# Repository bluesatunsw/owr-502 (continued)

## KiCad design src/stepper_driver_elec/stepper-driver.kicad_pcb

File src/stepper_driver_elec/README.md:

# Stepper Driver

A device to drive up to four high-current (10A peak, 5A continuous) bipolar stepper motors or eight brushed DC motors/solenoids. External sensors/low power devices may also be attached. It complies with the common device specification 2025-04.

## Steppers

Each stepper motor channel is driven by a TMC5160 controller. These controllers operate by driving two external full bridges, allowing for significantly more current to be delivered compared to devices with internal MOSFETs (such as the TMC2160).

Communication between the MCU and stepper controllers is performed using SPI. To allow for precise velocity control, the MCU provides a clock signal (using the MCO pin) to the clock input of the stepper drivers. Weak parallel termination (470R) is applied to reduce overshoot. The VSA rail of each controller is fed from the device 12V rail to reduce the heat generated by the internal linear regulators. For safety, the `DRV_ENN` pin of each stepper should be tied to a common line controlled by the MCU, externally pulled high.

The coils of the stepper motors are connected using a 4-pin JST-VH connector. A 6-pin JST-PA connector exposes the reference switch and A/B encoder pins of the controller, along with 3V3 and GND.

The TMC5160 datasheet states that 100u of capacitance per amp of output current is required; however, this requirement can be reduced significantly by using polymer capacitors, which have a very low ESR. A 220u capacitor (HV1H227M1010PZ) per channel should be sufficient.

### MOSFETs
| Manufacturer | Model        | Max Voltage | Peak Current | Continuous Current | RDS_on |
|--------------|--------------|-------------|--------------|--------------------|--------|
| Infineon     | BTN7030-1EPA | 28V         | 17A          |7A       | |

### Coil Pinout

| Pin | Signal | Colour |
| --- | ------ | ------ |
|  1  | `-A`   | Black  |
|  2  | `+A`   | Red    |
|  3  | `-B`   | Brown  |
|  4  | `+B`   | White  |

### Sensor Pinout

| Pin | Signal | Colour |
| --- | ------ | ------ |
|  1  | `GND`  | Black  |
|  2  | `VDD`  | Red    |
|  3  | `REFL` | Yellow |
|  4  | `REFR` | Green  |
|  5  | `ENCA` | Blue   |
|  6  | `ENCB` | Purple |

## Breakout Port

External sensors and low-power devices may be connected via a 24-pin JST-ZPD breakout header exposing:
- power from the VDD, 12V and VBUS;
- digital communication via I2C, SPI and UART/USART;
- digital GPIO including timer channels; and
- analog GPIO including op-amp and comparator channels.

The IO pins routed to the breakout port are not otherwise used for any other purpose.

**[TODO] Specify pinout**

## Internal Sensors

- Each stepper channel has an NTC thermistor (NCP15XH103F03RC) for temperature monitoring.
- A 6-axis IMU (ASM330LHH) and 3-axis magnetometer (LIS2MDL), both communicating over I2C, may optionally be installed to allow for groundstation use and advanced control modes.

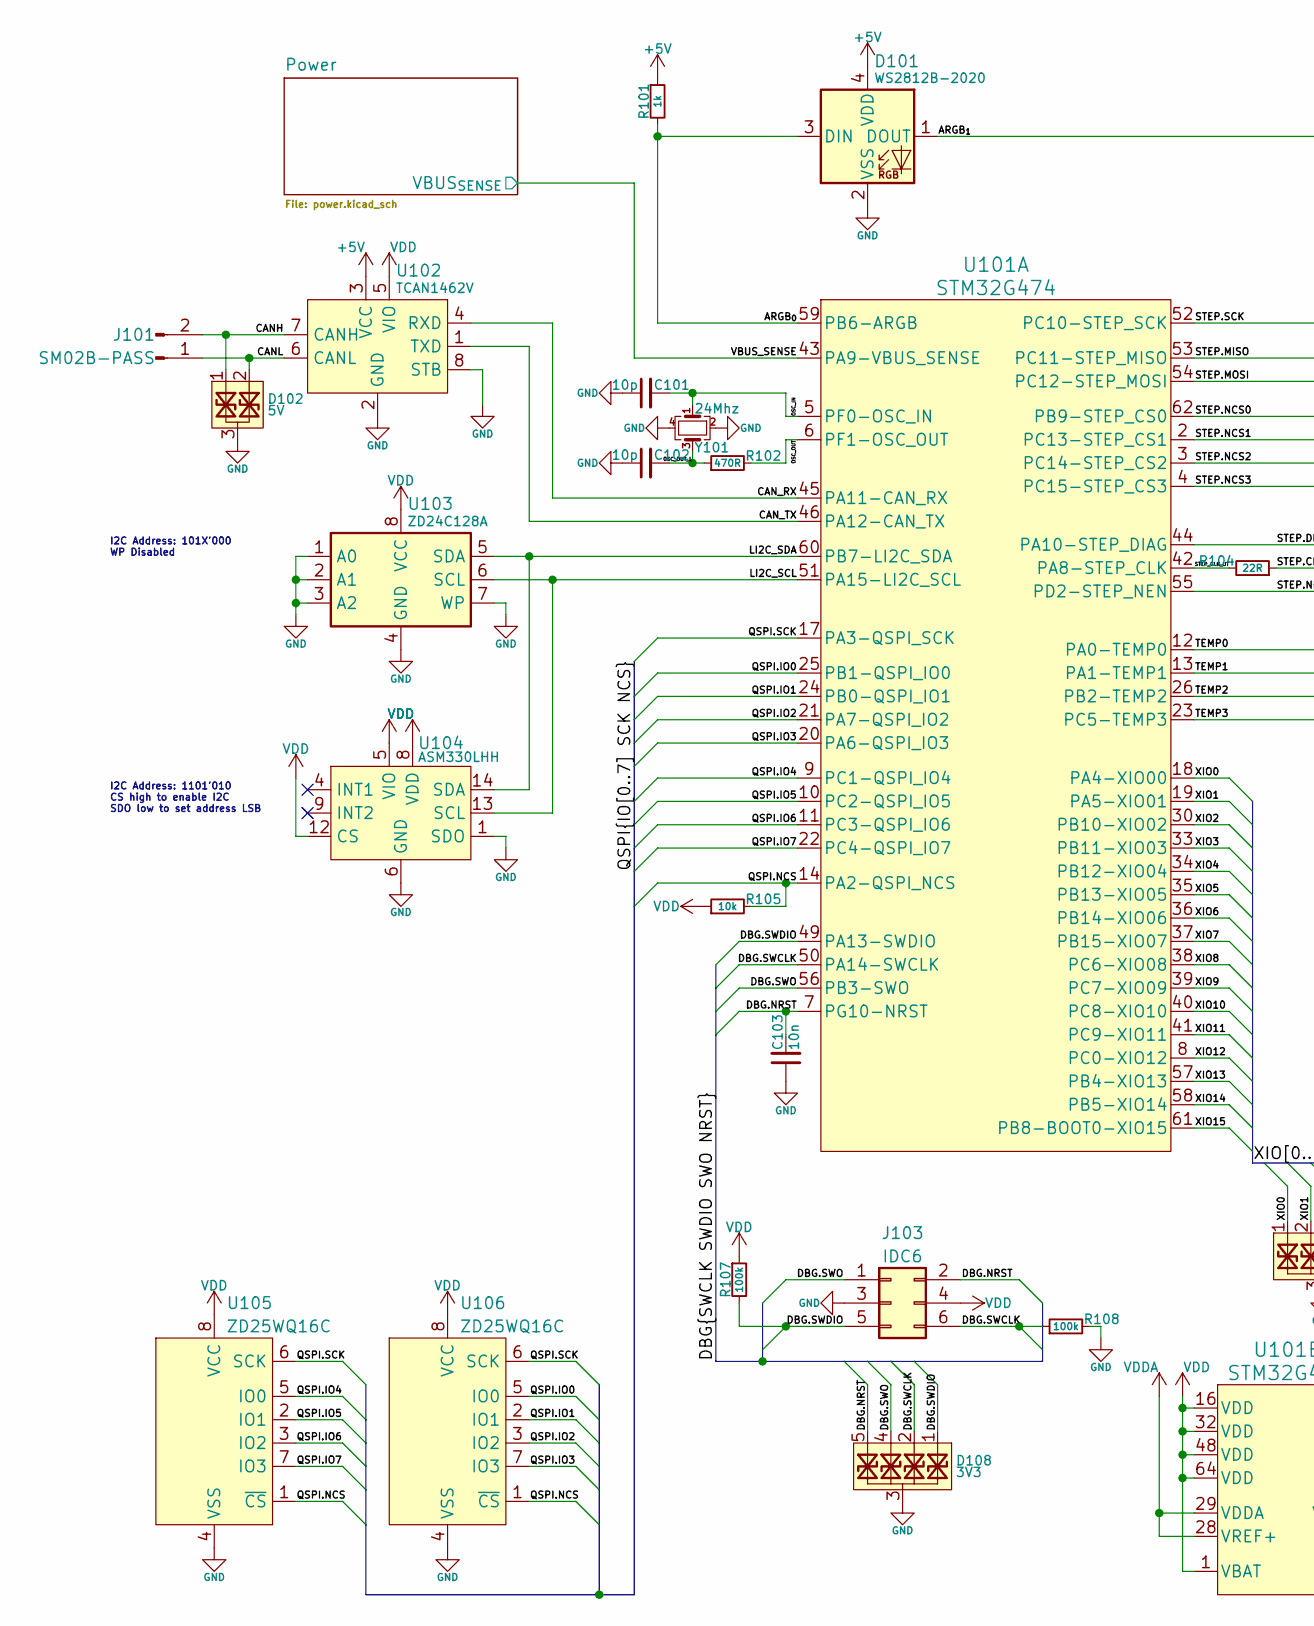
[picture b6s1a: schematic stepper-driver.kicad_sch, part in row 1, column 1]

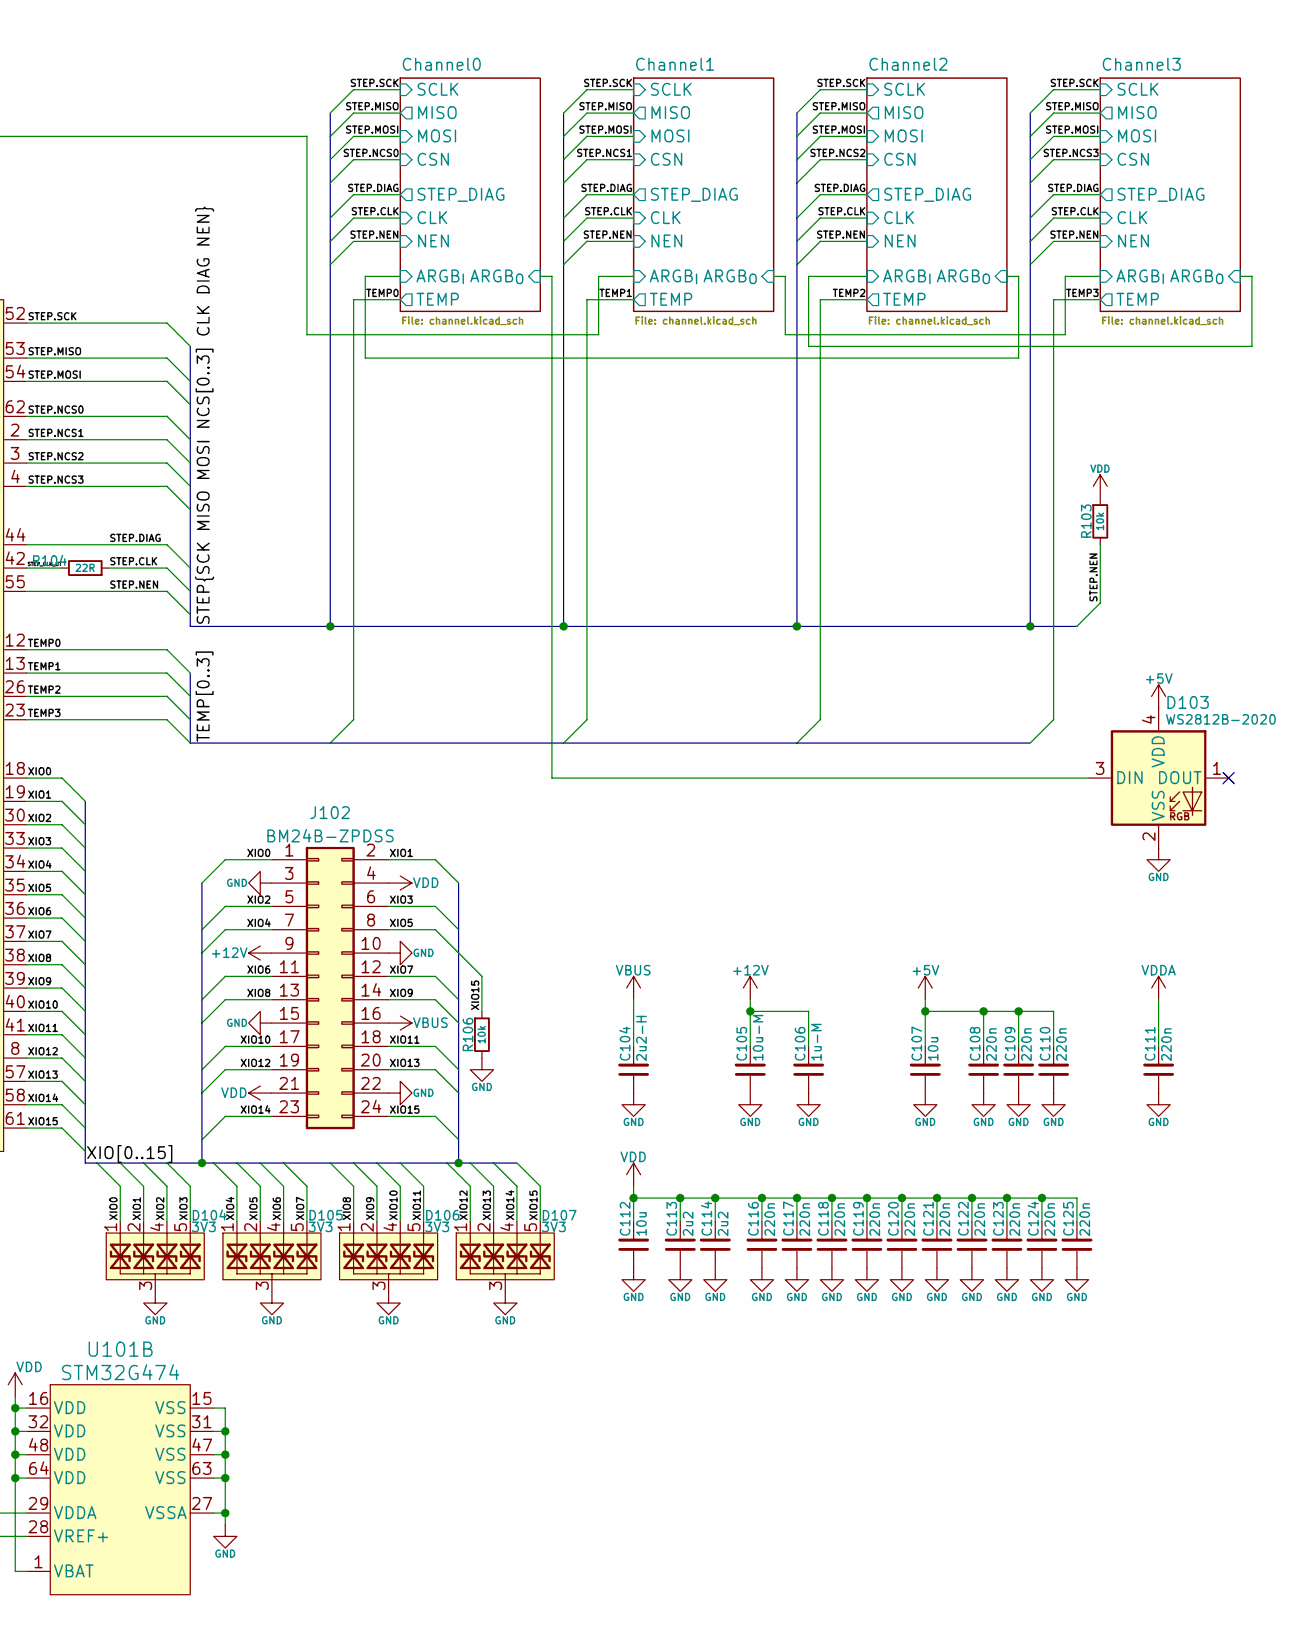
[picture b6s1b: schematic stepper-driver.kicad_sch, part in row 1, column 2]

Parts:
C101, C102: 10p; C_0402_1005Metric
C103: 10n; C_0402_1005Metric
C104: 2u2-H; C_1206_3216Metric
C105: 10u-M; C_1210_3225Metric
C106: 1u-M; C_0805_2012Metric
C107, C112: 10u; C_1206_3216Metric
C108, C109, C110, C111, C116, C117, C118, C119, C120, C121, C122, C123, C124, C125: 220n; C_0402_1005Metric
C113, C114: 2u2; C_0603_1608Metric
D101, D103: WS2812B-2020
D102: 5V; SOT-523
D104, D105, D106, D107, D108: 3V3; Diodes_UDFN-10_1x2.5mm_P0.5mm
J101: SM02B-PASS
J102: BM24B-ZPDSS
J103: IDC6
R101: 1k; R_0402_1005Metric
R102: 470R; R_0402_1005Metric
R103, R105, R106: 10k; R_0402_1005Metric
R104: 22R; R_0402_1005Metric
R107, R108: 100k; R_0402_1005Metric
U101: STM32G474; LQFP-64-0.5
U102: TCAN1462V; SOIC-8_3.9x4.9mm_P1.27mm
U103: ZD24C128A; TSSOP-8_4.4x3.0-0.65
U104: ASM330LHH; LGA-14_3x2.5mm_P0.5mm_LayoutBorder3x4y
U105, U106: ZD25WQ16C; Winbond_USON-8-1EP_3x2mm_P0.5mm_EP0.2x1.6mm
Y101: 24Mhz; Crystal_SMD_2016-4Pin_2.0x1.6mm

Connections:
+5V: C107.2, C108.2, C109.2, C110.2, D101.4 (VDD), D103.4 (VDD), R101.1, U102.3 (VCC); also elsewhere on the board
/ARGB_{0}: D101.3 (DIN), R101.2, U101.59 (PB6-ARGB)
/ARGB_{1}: D101.1 (DOUT); also elsewhere on the board
/CANH: D102.1, J101.2, U102.7 (CANH)
/CANL: D102.2, J101.1, U102.6 (CANL)
/CAN_RX: U101.45 (PA11-CAN_RX), U102.4 (RXD)
/CAN_TX: U101.46 (PA12-CAN_TX), U102.1 (TXD)
/Channel0/ARGB_{O}: D103.3 (DIN); also elsewhere on the board
/DBG.NRST: C103.2, D108.5, D108.6, J103.2, U101.7 (PG10-NRST)
/DBG.SWCLK: D108.2, D108.9, J103.6, R108.1, U101.50 (PA14-SWCLK)
/DBG.SWDIO: D108.1, D108.10, J103.5, R107.2, U101.49 (PA13-SWDIO)
/DBG.SWO: D108.4, D108.7, J103.1, U101.56 (PB3-SWO)
/LI2C_SCL: U101.51 (PA15-LI2C_SCL), U103.6 (SCL), U104.13 (SCL)
/LI2C_SDA: U101.60 (PB7-LI2C_SDA), U103.5 (SDA), U104.14 (SDA)
/OSC_IN: C101.2, U101.5 (PF0-OSC_IN), Y101.1
/OSC_OUT: R102.2, U101.6 (PF1-OSC_OUT)
/OSC_OUT_L: C102.2, R102.1, Y101.3
/QSPI.IO0: U101.25 (PB1-QSPI_IO0), U106.5 (IO0)
/QSPI.IO1: U101.24 (PB0-QSPI_IO1), U106.2 (IO1)
/QSPI.IO2: U101.21 (PA7-QSPI_IO2), U106.3 (IO2)
/QSPI.IO3: U101.20 (PA6-QSPI_IO3), U106.7 (IO3)
/QSPI.IO4: U101.9 (PC1-QSPI_IO4), U105.5 (IO0)
/QSPI.IO5: U101.10 (PC2-QSPI_IO5), U105.2 (IO1)
/QSPI.IO6: U101.11 (PC3-QSPI_IO6), U105.3 (IO2)
/QSPI.IO7: U101.22 (PC4-QSPI_IO7), U105.7 (IO3)
/QSPI.NCS: R105.2, U101.14 (PA2-QSPI_NCS), U105.1 (~CS), U106.1 (~CS)
/QSPI.SCK: U101.17 (PA3-QSPI_SCK), U105.6 (SCK), U106.6 (SCK)
/STEP.CLK: R104.1; also elsewhere on the board
/STEP.DIAG: U101.44 (PA10-STEP_DIAG); also elsewhere on the board
/STEP.MISO: U101.53 (PC11-STEP_MISO); also elsewhere on the board
/STEP.MOSI: U101.54 (PC12-STEP_MOSI); also elsewhere on the board
/STEP.NCS0: U101.62 (PB9-STEP_CS0); also elsewhere on the board
/STEP.NCS1: U101.2 (PC13-STEP_CS1); also elsewhere on the board
/STEP.NCS2: U101.3 (PC14-STEP_CS2); also elsewhere on the board
/STEP.NCS3: U101.4 (PC15-STEP_CS3); also elsewhere on the board
/STEP.NEN: R103.2, U101.55 (PD2-STEP_NEN); also elsewhere on the board
/STEP.SCK: U101.52 (PC10-STEP_SCK); also elsewhere on the board
/STEP_CLK_UT: R104.2, U101.42 (PA8-STEP_CLK)
/TEMP0: U101.12 (PA0-TEMP0); also elsewhere on the board
/TEMP1: U101.13 (PA1-TEMP1); also elsewhere on the board
/TEMP2: U101.26 (PB2-TEMP2); also elsewhere on the board
/TEMP3: U101.23 (PC5-TEMP3); also elsewhere on the board
/VBUS_SENSE: U101.43 (PA9-VBUS_SENSE); also elsewhere on the board
/XIO0: D104.1, D104.10, J102.1, U101.18 (PA4-XIO00)
/XIO1: D104.2, D104.9, J102.2, U101.19 (PA5-XIO01)
/XIO2: D104.4, D104.7, J102.5, U101.30 (PB10-XIO02)
/XIO3: D104.5, D104.6, J102.6, U101.33 (PB11-XIO03)
/XIO4: D105.1, D105.10, J102.7, U101.34 (PB12-XIO04)
/XIO5: D105.2, D105.9, J102.8, U101.35 (PB13-XIO05)
/XIO6: D105.4, D105.7, J102.11, U101.36 (PB14-XIO06)
/XIO7: D105.5, D105.6, J102.12, U101.37 (PB15-XIO07)
/XIO8: D106.1, D106.10, J102.13, U101.38 (PC6-XIO08)
/XIO9: D106.2, D106.9, J102.14, U101.39 (PC7-XIO09)
/XIO10: D106.4, D106.7, J102.17, U101.40 (PC8-XIO10)
/XIO11: D106.5, D106.6, J102.18, U101.41 (PC9-XIO11)
/XIO12: D107.1, D107.10, J102.19, U101.8 (PC0-XIO12)
/XIO13: D107.2, D107.9, J102.20, U101.57 (PB4-XIO13)
/XIO14: D107.4, D107.7, J102.23, U101.58 (PB5-XIO14)
/XIO15: D107.5, D107.6, J102.24, R106.1, U101.61 (PB8-BOOT0-XIO15)
GND: C101.1, C102.1, C103.1, C104.1, C105.1, C106.1, C107.1, C108.1, C109.1, C110.1, C111.1, C112.1, C113.1, C114.1, C116.1, C117.1, C118.1, C119.1, C120.1, C121.1, C122.1, C123.1, C124.1, C125.1, D101.2 (VSS), D102.3, D103.2 (VSS), D104.3, D104.8, D105.3, D105.8, D106.3, D106.8, D107.3, D107.8, D108.3, D108.8, J102.3, J102.10, J102.15, J102.22, J103.3, R106.2, R108.2, U101.15 (VSS), U101.27 (VSSA), U101.31 (VSS), U101.47 (VSS), U101.63 (VSS), U102.2 (GND), U102.8 (STB), U102.9 (EP), U103.1 (A0), U103.2 (A1), U103.3 (A2), U103.4 (GND), U103.7 (WP), U104.1 (SDO), U104.2 (RES), U104.3 (RES), U104.6 (GND), U104.7 (GND), U105.4 (VSS), U106.4 (VSS), Y101.2, Y101.4; also elsewhere on the board
VBUS: C104.2, J102.16; also elsewhere on the board
VDDA: C111.2, U101.28 (VREF+), U101.29 (VDDA); also elsewhere on the board

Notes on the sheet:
I2C Address: 101X'000 WP Disabled
I2C Address: 1101'010 CS high to enable I2C SDO low to set address LSB

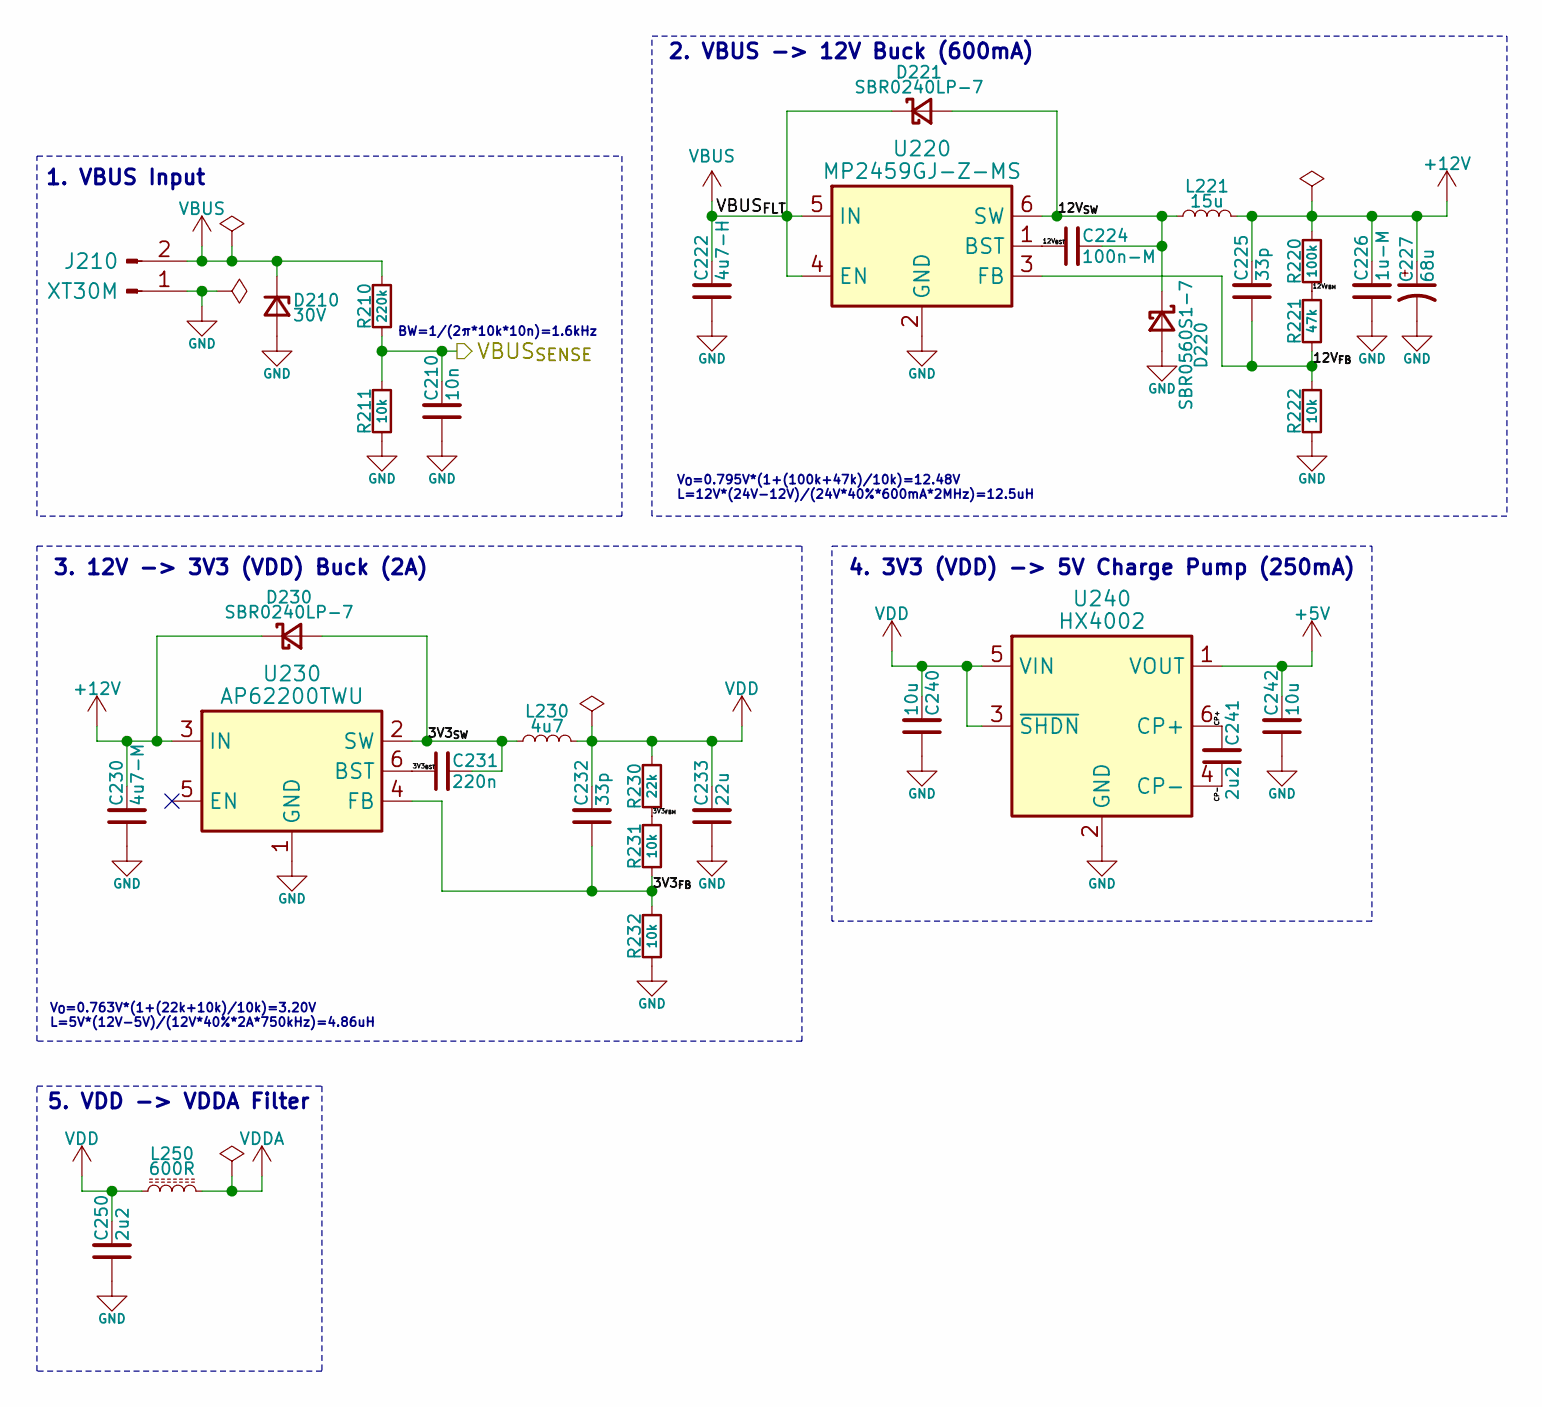
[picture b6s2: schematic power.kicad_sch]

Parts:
C210: 10n; C_0402_1005Metric
C222: 4u7-H; C_1210_3225Metric
C224: 100n-M; C_0402_1005Metric
C225, C232: 33p; C_0402_1005Metric
C226: 1u-M; C_0805_2012Metric
C227: 68u; CP_Elec_6.3x7.7
C230: 4u7-M; C_1206_3216Metric
C231: 220n; C_0402_1005Metric
C233: 22u; C_1210_3225Metric
C240, C242: 10u; C_1206_3216Metric
C241, C250: 2u2; C_0603_1608Metric
D210: 30V; D_SOD-123F
D220: SBR0560S1-7; D_SOD-123
D221, D230: SBR0240LP-7; D_SOD-882
J210: XT30M; AMASS_XT30PW-M_1x02_P2.50mm_Horizontal
L221: 15u; L_Changjiang_FNR5040S
L230: 4u7; L_Changjiang_FNR4020S
L250: 600R; R_0402_1005Metric
R210: 220k; R_0402_1005Metric
R211, R222, R231, R232: 10k; R_0402_1005Metric
R220: 100k; R_0402_1005Metric
R221: 47k; R_0402_1005Metric
R230: 22k; R_0402_1005Metric
U220: MP2459GJ-Z-MS; TSOT-23-6
U230: AP62200TWU; TSOT-23-6
U240: HX4002; SOT-23-6

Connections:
+5V: C242.2, U240.1 (VOUT); also elsewhere on the board
/Power/3V3_{BST}: C231.1, U230.6 (BST)
/Power/3V3_{FBM}: R230.2, R231.1
/Power/3V3_{FB}: C232.1, R231.2, R232.1, U230.4 (FB)
/Power/12V_{BST}: C224.1, U220.1 (BST)
/Power/12V_{FBM}: R220.2, R221.1
/Power/12V_{FB}: C225.1, R221.2, R222.1, U220.3 (FB)
/Power/CP+: C241.2, U240.6 (CP+)
/Power/CP-: C241.1, U240.4 (CP-)
/VBUS_SENSE: C210.2, R210.2, R211.1; also elsewhere on the board
GND: C210.1, C222.1, C226.1, C227.2, C230.1, C233.1, C240.1, C242.1, C250.1, D210.2 (A), D220.2 (A), J210.1, R211.2, R222.2, R232.2, U220.2 (GND), U230.1 (GND), U240.2 (GND); also elsewhere on the board
VBUS: C222.2, D210.1 (K), D221.1 (K), J210.2, R210.1, U220.4 (EN), U220.5 (IN); also elsewhere on the board
VDDA: L250.2; also elsewhere on the board

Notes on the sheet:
2. VBUS -> 12V Buck (600mA)
V_{O}=0.795V*(1+(100k+47k)/10k)=12.48V L=12V*(24V-12V)/(24V*40%*600mA*2MHz)=12.5uH
4. 3V3 (VDD) -> 5V Charge Pump (250mA)
1. VBUS Input
BW=1/(2π*10k*10n)=1.6kHz
V_{O}=0.763V*(1+(22k+10k)/10k)=3.20V L=5V*(12V-5V)/(12V*40%*2A*750kHz)=4.86uH
3. 12V -> 3V3 (VDD) Buck (2A)
5. VDD -> VDDA Filter

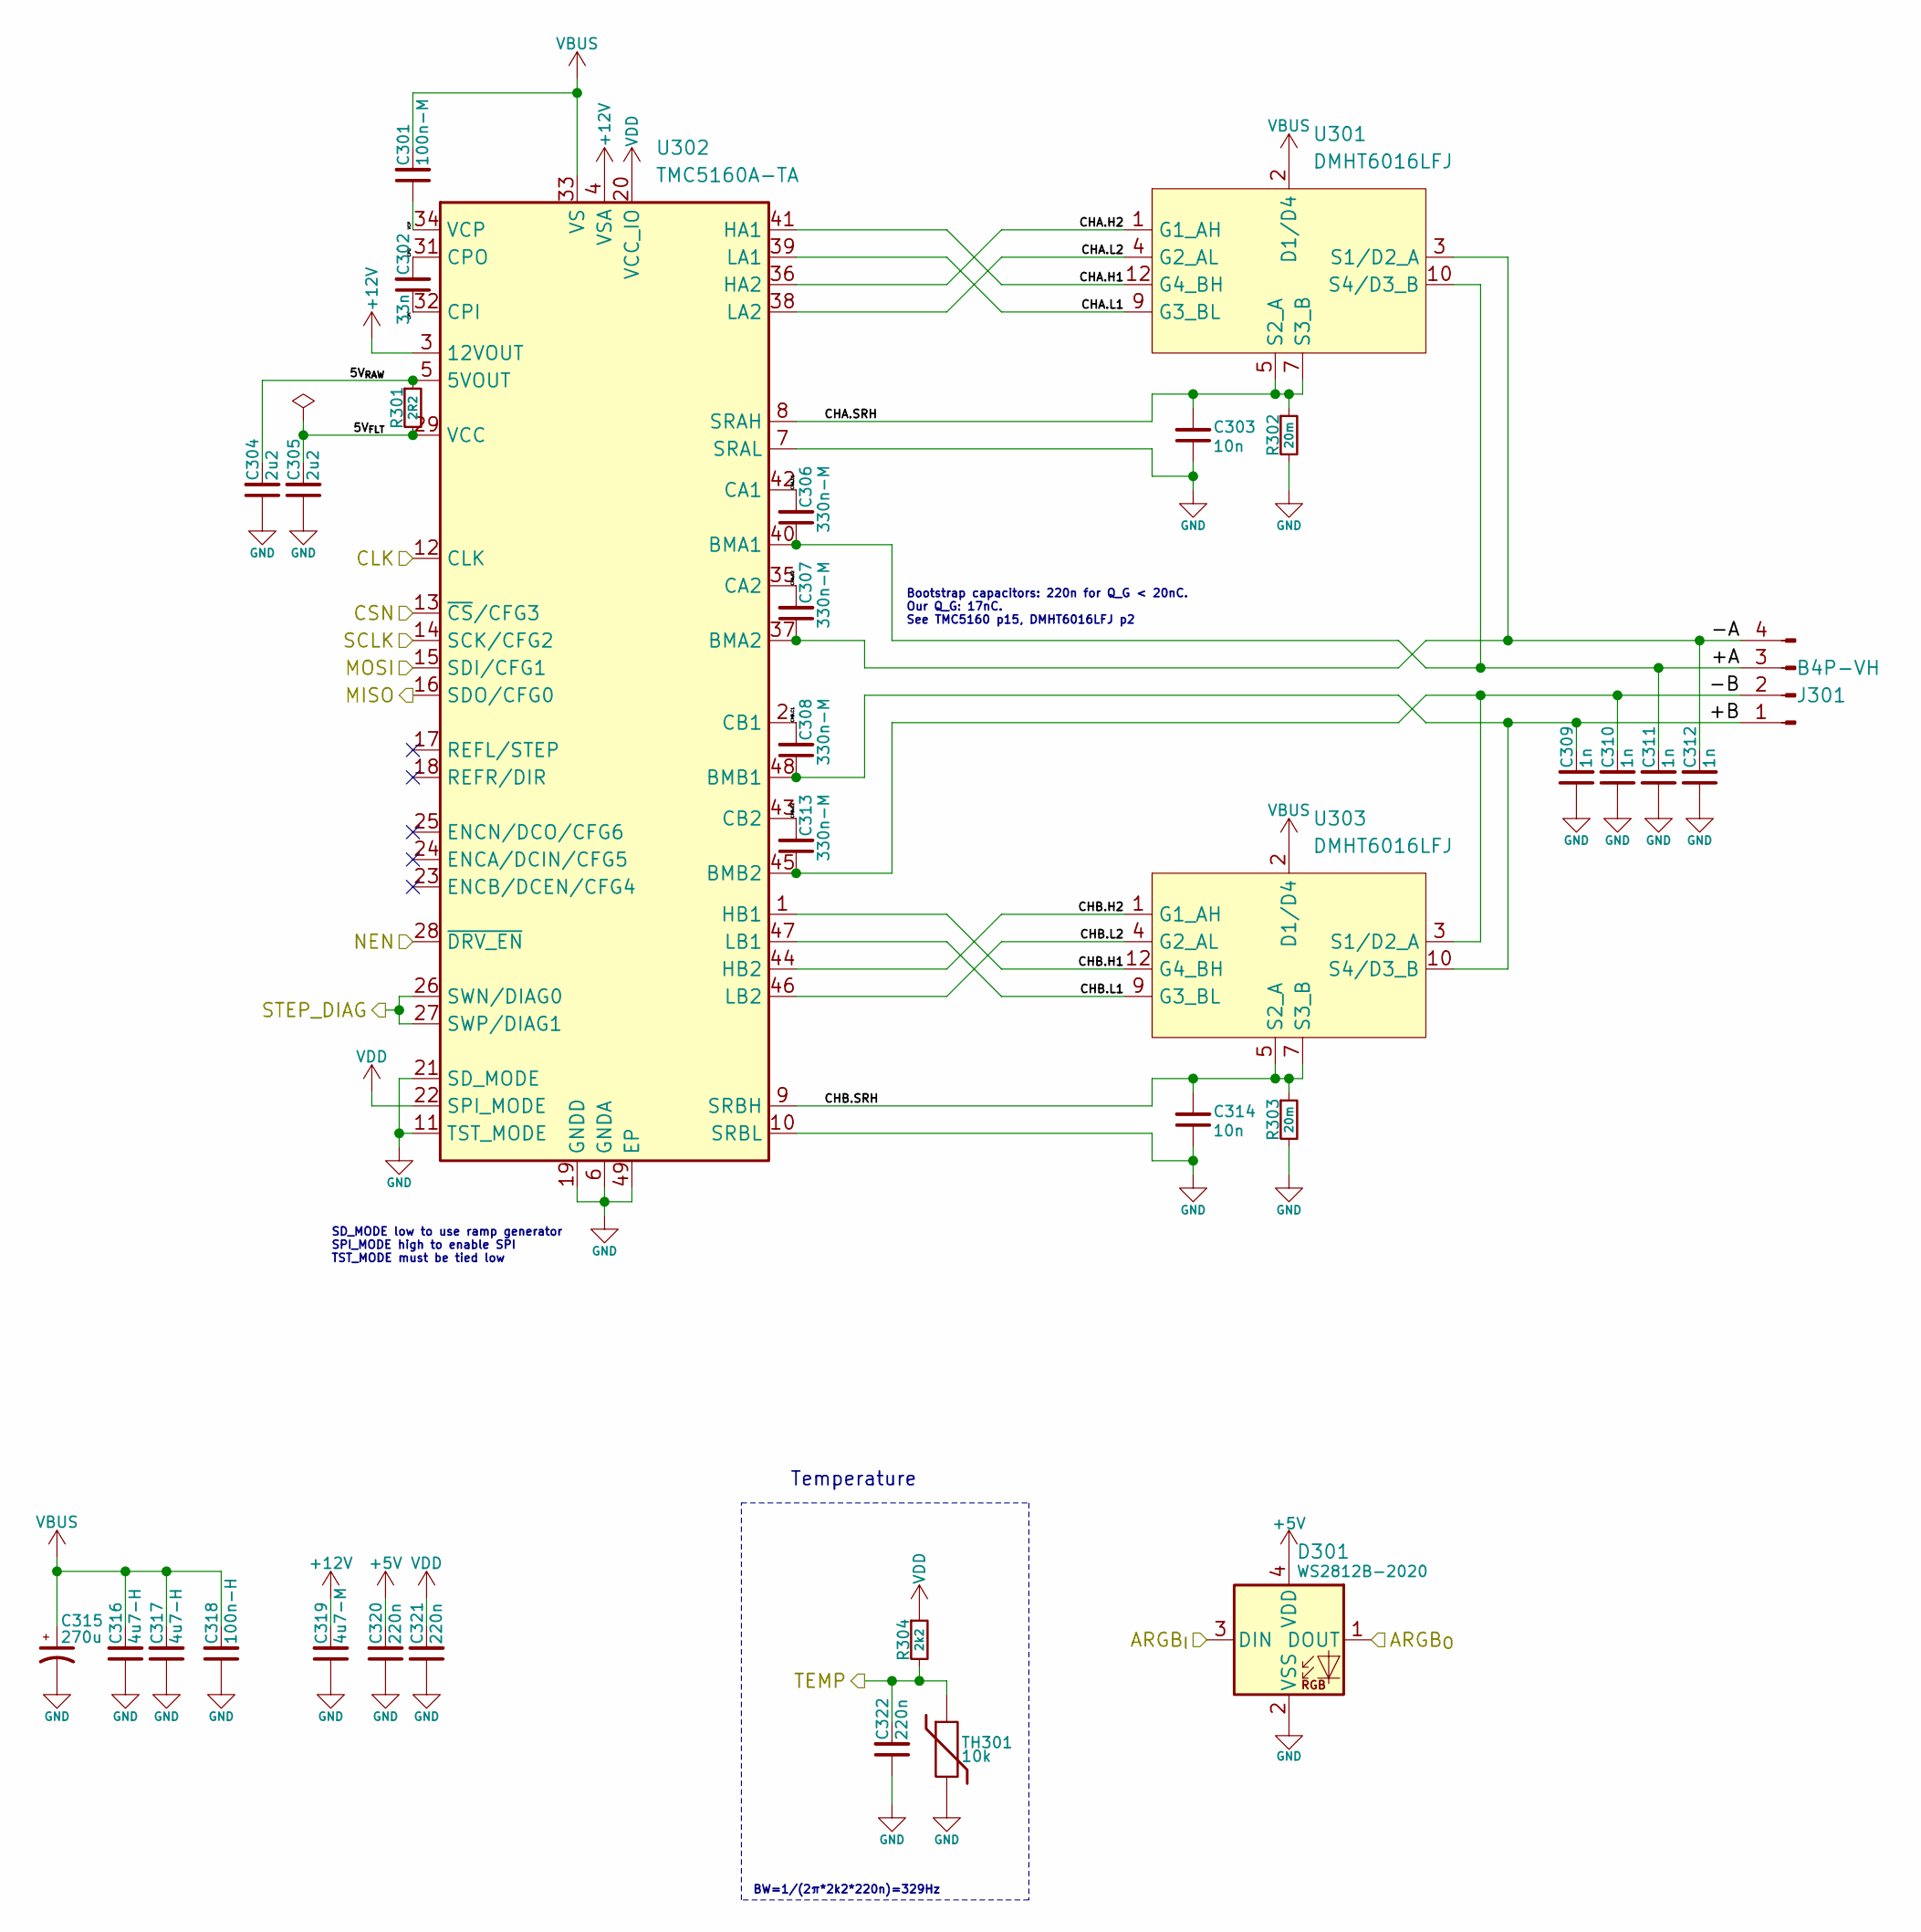
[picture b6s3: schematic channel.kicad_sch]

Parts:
C301: 100n-M; C_0402_1005Metric
C302: 33n; C_0402_1005Metric
C303, C314: 10n; C_0402_1005Metric
C304, C305: 2u2; C_0603_1608Metric
C306, C307, C308, C313: 330n-M; C_0603_1608Metric
C309, C310, C311, C312: 1n; C_0402_1005Metric
C315: 270u; CP_Elec_10x10
C316, C317: 4u7-H; C_1210_3225Metric
C318: 100n-H; C_0603_1608Metric
C319: 4u7-M; C_1210_3225Metric
C320, C321, C322: 220n; C_0402_1005Metric
D301: WS2812B-2020
J301: B4P-VH
R301: 2R2; R_0402_1005Metric
R302, R303: 20m; R_2512_6332Metric
R304: 2k2; R_0402_1005Metric
TH301: 10k; R_0402_1005Metric
U301, U303: DMHT6016LFJ; VDFN5045-12
U302: TMC5160A-TA; TQFP-48-0.5-EP

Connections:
+5V: C320.2, D301.4 (VDD); also elsewhere on the board
/Channel0/5V_{FLT}: C305.2, R301.2, U302.29 (VCC)
/Channel0/5V_{RAW}: C304.2, R301.1, U302.5 (5VOUT)
/Channel0/+A: C306.1, C311.2, J301.3, U301.10 (S4/D3_B), U301.C (S4/D3_B), U302.40 (BMA1)
/Channel0/+B: C308.1, C309.2, J301.1, U302.48 (BMB1), U303.10 (S4/D3_B), U303.C (S4/D3_B)
/Channel0/-A: C307.1, C312.2, J301.4, U301.3 (S1/D2_A), U301.B (S1/D2_A), U302.37 (BMA2)
/Channel0/-B: C310.2, C313.1, J301.2, U302.45 (BMB2), U303.3 (S1/D2_A), U303.B (S1/D2_A)
/Channel0/ARGB_{I}: D301.3 (DIN); also elsewhere on the board
/Channel0/ARGB_{O}: D301.1 (DOUT); also elsewhere on the board
/Channel0/CHA.C1: C306.2, U302.42 (CA1)
/Channel0/CHA.C2: C307.2, U302.35 (CA2)
/Channel0/CHA.H1: U301.12 (G4_BH), U302.41 (HA1)
/Channel0/CHA.H2: U301.1 (G1_AH), U302.36 (HA2)
/Channel0/CHA.L1: U301.9 (G3_BL), U302.39 (LA1)
/Channel0/CHA.L2: U301.4 (G2_AL), U302.38 (LA2)
/Channel0/CHA.SRH: C303.2, R302.1, U301.5 (S2_A), U301.6 (S2_A), U301.7 (S3_B), U301.8 (S3_B), U302.8 (SRAH)
/Channel0/CHB.C1: C308.2, U302.2 (CB1)
/Channel0/CHB.C2: C313.2, U302.43 (CB2)
/Channel0/CHB.H1: U302.1 (HB1), U303.12 (G4_BH)
/Channel0/CHB.H2: U302.44 (HB2), U303.1 (G1_AH)
/Channel0/CHB.L1: U302.47 (LB1), U303.9 (G3_BL)
/Channel0/CHB.L2: U302.46 (LB2), U303.4 (G2_AL)
/Channel0/CHB.SRH: C314.2, R303.1, U302.9 (SRBH), U303.5 (S2_A), U303.6 (S2_A), U303.7 (S3_B), U303.8 (S3_B)
/Channel0/CPI: C302.1, U302.32 (CPI)
/Channel0/CPO: C302.2, U302.31 (CPO)
/Channel0/VCP: C301.1, U302.34 (VCP)
/STEP.CLK: U302.12 (CLK); also elsewhere on the board
/STEP.DIAG: U302.26 (SWN/DIAG0), U302.27 (SWP/DIAG1); also elsewhere on the board
/STEP.MISO: U302.16 (SDO/CFG0); also elsewhere on the board
/STEP.MOSI: U302.15 (SDI/CFG1); also elsewhere on the board
/STEP.NCS0: U302.13 (~CS/CFG3); also elsewhere on the board
/STEP.NEN: U302.28 (~DRV_EN); also elsewhere on the board
/STEP.SCK: U302.14 (SCK/CFG2); also elsewhere on the board
/TEMP0: C322.2, R304.2, TH301.1; also elsewhere on the board
GND: C303.1, C304.1, C305.1, C309.1, C310.1, C311.1, C312.1, C314.1, C315.2, C316.1, C317.1, C318.1, C319.1, C320.1, C321.1, C322.1, D301.2 (VSS), R302.2, R303.2, TH301.2, U302.6 (GNDA), U302.7 (SRAL), U302.10 (SRBL), U302.11 (TST_MODE), U302.19 (GNDD), U302.21 (SD_MODE), U302.30 (GNDD), U302.49 (EP); also elsewhere on the board
VBUS: C301.2, C315.1, C316.2, C317.2, C318.2, U301.2 (D1/D4), U301.11 (D1/D4), U301.A (D1/D4), U302.33 (VS), U303.2 (D1/D4), U303.11 (D1/D4), U303.A (D1/D4); also elsewhere on the board

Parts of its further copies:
C401, C501, C601: 100n-H; C_0603_1608Metric
C402, C502, C602: 100n-M; C_0402_1005Metric
C403, C503, C603: 33n; C_0402_1005Metric
C404, C416, C504, C516, C604, C616: 10n; C_0402_1005Metric
C406, C407, C506, C507, C606, C607: 2u2; C_0603_1608Metric
C408, C409, C410, C415, C508, C509, C510, C515, C608, C609, C610, C615: 330n-M; C_0603_1608Metric
C411, C412, C413, C414, C511, C512, C513, C514, C611, C612, C613, C614: 1n; C_0402_1005Metric
C419, C420, C426, C519, C520, C526, C619, C620, C626: 220n; C_0402_1005Metric
C421, C521, C621: 4u7-M; C_1210_3225Metric
C422, C522, C622: 270u; CP_Elec_10x10
C424, C425, C524, C525, C624, C625: 4u7-H; C_1210_3225Metric
D402, D502, D602: WS2812B-2020
J401, J501, J601: B4P-VH
R407, R507, R607: 2R2; R_0402_1005Metric
R408, R415, R508, R515, R608, R615: 20m; R_2512_6332Metric
R417, R517, R617: 2k2; R_0402_1005Metric
TH401, TH501, TH601: 10k; R_0402_1005Metric
U401, U403, U501, U503, U601, U603: DMHT6016LFJ; VDFN5045-12
U402, U502, U602: TMC5160A-TA; TQFP-48-0.5-EP

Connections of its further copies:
+5V: C420.2, C520.2, C620.2, D402.4 (VDD), D502.4 (VDD), D602.4 (VDD); also elsewhere on the board
/ARGB_{1}: D402.3 (DIN); also elsewhere on the board
/Channel0/ARGB_{I}: D502.1 (DOUT); also elsewhere on the board
/Channel1/5V_{FLT}: C407.2, R407.2, U402.29 (VCC)
/Channel1/5V_{RAW}: C406.2, R407.1, U402.5 (5VOUT)
/Channel1/+A: C408.1, C413.2, J401.3, U401.10 (S4/D3_B), U401.C (S4/D3_B), U402.40 (BMA1)
/Channel1/+B: C410.1, C411.2, J401.1, U402.48 (BMB1), U403.10 (S4/D3_B), U403.C (S4/D3_B)
/Channel1/-A: C409.1, C414.2, J401.4, U401.3 (S1/D2_A), U401.B (S1/D2_A), U402.37 (BMA2)
/Channel1/-B: C412.2, C415.1, J401.2, U402.45 (BMB2), U403.3 (S1/D2_A), U403.B (S1/D2_A)
/Channel1/ARGB_{O}: D402.1 (DOUT), D602.3 (DIN)
/Channel1/CHA.C1: C408.2, U402.42 (CA1)
/Channel1/CHA.C2: C409.2, U402.35 (CA2)
/Channel1/CHA.H1: U401.12 (G4_BH), U402.41 (HA1)
/Channel1/CHA.H2: U401.1 (G1_AH), U402.36 (HA2)
/Channel1/CHA.L1: U401.9 (G3_BL), U402.39 (LA1)
/Channel1/CHA.L2: U401.4 (G2_AL), U402.38 (LA2)
/Channel1/CHA.SRH: C404.2, R408.1, U401.5 (S2_A), U401.6 (S2_A), U401.7 (S3_B), U401.8 (S3_B), U402.8 (SRAH)
/Channel1/CHB.C1: C410.2, U402.2 (CB1)
/Channel1/CHB.C2: C415.2, U402.43 (CB2)
/Channel1/CHB.H1: U402.1 (HB1), U403.12 (G4_BH)
/Channel1/CHB.H2: U402.44 (HB2), U403.1 (G1_AH)
/Channel1/CHB.L1: U402.47 (LB1), U403.9 (G3_BL)
/Channel1/CHB.L2: U402.46 (LB2), U403.4 (G2_AL)
/Channel1/CHB.SRH: C416.2, R415.1, U402.9 (SRBH), U403.5 (S2_A), U403.6 (S2_A), U403.7 (S3_B), U403.8 (S3_B)
/Channel1/CPI: C403.1, U402.32 (CPI)
/Channel1/CPO: C403.2, U402.31 (CPO)
/Channel1/VCP: C402.1, U402.34 (VCP)
/Channel2/5V_{FLT}: C507.2, R507.2, U502.29 (VCC)
/Channel2/5V_{RAW}: C506.2, R507.1, U502.5 (5VOUT)
/Channel2/+A: C508.1, C513.2, J501.3, U501.10 (S4/D3_B), U501.C (S4/D3_B), U502.40 (BMA1)
/Channel2/+B: C510.1, C511.2, J501.1, U502.48 (BMB1), U503.10 (S4/D3_B), U503.C (S4/D3_B)
/Channel2/-A: C509.1, C514.2, J501.4, U501.3 (S1/D2_A), U501.B (S1/D2_A), U502.37 (BMA2)
/Channel2/-B: C512.2, C515.1, J501.2, U502.45 (BMB2), U503.3 (S1/D2_A), U503.B (S1/D2_A)
/Channel2/ARGB_{I}: D502.3 (DIN), D602.1 (DOUT)
/Channel2/CHA.C1: C508.2, U502.42 (CA1)
/Channel2/CHA.C2: C509.2, U502.35 (CA2)
/Channel2/CHA.H1: U501.12 (G4_BH), U502.41 (HA1)
/Channel2/CHA.H2: U501.1 (G1_AH), U502.36 (HA2)
/Channel2/CHA.L1: U501.9 (G3_BL), U502.39 (LA1)
/Channel2/CHA.L2: U501.4 (G2_AL), U502.38 (LA2)
/Channel2/CHA.SRH: C504.2, R508.1, U501.5 (S2_A), U501.6 (S2_A), U501.7 (S3_B), U501.8 (S3_B), U502.8 (SRAH)
/Channel2/CHB.C1: C510.2, U502.2 (CB1)
/Channel2/CHB.C2: C515.2, U502.43 (CB2)
/Channel2/CHB.H1: U502.1 (HB1), U503.12 (G4_BH)
/Channel2/CHB.H2: U502.44 (HB2), U503.1 (G1_AH)
/Channel2/CHB.L1: U502.47 (LB1), U503.9 (G3_BL)
/Channel2/CHB.L2: U502.46 (LB2), U503.4 (G2_AL)
/Channel2/CHB.SRH: C516.2, R515.1, U502.9 (SRBH), U503.5 (S2_A), U503.6 (S2_A), U503.7 (S3_B), U503.8 (S3_B)
/Channel2/CPI: C503.1, U502.32 (CPI)
/Channel2/CPO: C503.2, U502.31 (CPO)
/Channel2/VCP: C502.1, U502.34 (VCP)
/Channel3/5V_{FLT}: C607.2, R607.2, U602.29 (VCC)
/Channel3/5V_{RAW}: C606.2, R607.1, U602.5 (5VOUT)
/Channel3/+A: C608.1, C613.2, J601.3, U601.10 (S4/D3_B), U601.C (S4/D3_B), U602.40 (BMA1)
/Channel3/+B: C610.1, C611.2, J601.1, U602.48 (BMB1), U603.10 (S4/D3_B), U603.C (S4/D3_B)
/Channel3/-A: C609.1, C614.2, J601.4, U601.3 (S1/D2_A), U601.B (S1/D2_A), U602.37 (BMA2)
/Channel3/-B: C612.2, C615.1, J601.2, U602.45 (BMB2), U603.3 (S1/D2_A), U603.B (S1/D2_A)
/Channel3/CHA.C1: C608.2, U602.42 (CA1)
/Channel3/CHA.C2: C609.2, U602.35 (CA2)
/Channel3/CHA.H1: U601.12 (G4_BH), U602.41 (HA1)
/Channel3/CHA.H2: U601.1 (G1_AH), U602.36 (HA2)
/Channel3/CHA.L1: U601.9 (G3_BL), U602.39 (LA1)
/Channel3/CHA.L2: U601.4 (G2_AL), U602.38 (LA2)
/Channel3/CHA.SRH: C604.2, R608.1, U601.5 (S2_A), U601.6 (S2_A), U601.7 (S3_B), U601.8 (S3_B), U602.8 (SRAH)
/Channel3/CHB.C1: C610.2, U602.2 (CB1)
/Channel3/CHB.C2: C615.2, U602.43 (CB2)
/Channel3/CHB.H1: U602.1 (HB1), U603.12 (G4_BH)
/Channel3/CHB.H2: U602.44 (HB2), U603.1 (G1_AH)
/Channel3/CHB.L1: U602.47 (LB1), U603.9 (G3_BL)
/Channel3/CHB.L2: U602.46 (LB2), U603.4 (G2_AL)
/Channel3/CHB.SRH: C616.2, R615.1, U602.9 (SRBH), U603.5 (S2_A), U603.6 (S2_A), U603.7 (S3_B), U603.8 (S3_B)
/Channel3/CPI: C603.1, U602.32 (CPI)
/Channel3/CPO: C603.2, U602.31 (CPO)
/Channel3/VCP: C602.1, U602.34 (VCP)
/STEP.CLK: U402.12 (CLK), U502.12 (CLK), U602.12 (CLK); also elsewhere on the board
/STEP.DIAG: U402.26 (SWN/DIAG0), U402.27 (SWP/DIAG1), U502.26 (SWN/DIAG0), U502.27 (SWP/DIAG1), U602.26 (SWN/DIAG0), U602.27 (SWP/DIAG1); also elsewhere on the board
/STEP.MISO: U402.16 (SDO/CFG0), U502.16 (SDO/CFG0), U602.16 (SDO/CFG0); also elsewhere on the board
/STEP.MOSI: U402.15 (SDI/CFG1), U502.15 (SDI/CFG1), U602.15 (SDI/CFG1); also elsewhere on the board
/STEP.NCS1: U402.13 (~CS/CFG3); also elsewhere on the board
/STEP.NCS2: U502.13 (~CS/CFG3); also elsewhere on the board
/STEP.NCS3: U602.13 (~CS/CFG3); also elsewhere on the board
/STEP.NEN: U402.28 (~DRV_EN), U502.28 (~DRV_EN), U602.28 (~DRV_EN); also elsewhere on the board
/STEP.SCK: U402.14 (SCK/CFG2), U502.14 (SCK/CFG2), U602.14 (SCK/CFG2); also elsewhere on the board
/TEMP1: C426.2, R417.2, TH401.1; also elsewhere on the board
/TEMP2: C526.2, R517.2, TH501.1; also elsewhere on the board
/TEMP3: C626.2, R617.2, TH601.1; also elsewhere on the board
GND: C401.1, C404.1, C406.1, C407.1, C411.1, C412.1, C413.1, C414.1, C416.1, C419.1, C420.1, C421.1, C422.2, C424.1, C425.1, C426.1, C501.1, C504.1, C506.1, C507.1, C511.1, C512.1, C513.1, C514.1, C516.1, C519.1, C520.1, C521.1, C522.2, C524.1, C525.1, C526.1, C601.1, C604.1, C606.1, C607.1, C611.1, C612.1, C613.1, C614.1, C616.1, C619.1, C620.1, C621.1, C622.2, C624.1, C625.1, C626.1, D402.2 (VSS), D502.2 (VSS), D602.2 (VSS), R408.2, R415.2, R508.2, R515.2, R608.2, R615.2, TH401.2, TH501.2, TH601.2, U402.6 (GNDA), U402.7 (SRAL), U402.10 (SRBL), U402.11 (TST_MODE), U402.19 (GNDD), U402.21 (SD_MODE), U402.30 (GNDD), U402.49 (EP), U502.6 (GNDA), U502.7 (SRAL), U502.10 (SRBL), U502.11 (TST_MODE), U502.19 (GNDD), U502.21 (SD_MODE), U502.30 (GNDD), U502.49 (EP), U602.6 (GNDA), U602.7 (SRAL), U602.10 (SRBL), U602.11 (TST_MODE), U602.19 (GNDD), U602.21 (SD_MODE), U602.30 (GNDD), U602.49 (EP); also elsewhere on the board
VBUS: C401.2, C402.2, C422.1, C424.2, C425.2, C501.2, C502.2, C522.1, C524.2, C525.2, C601.2, C602.2, C622.1, C624.2, C625.2, U401.2 (D1/D4), U401.11 (D1/D4), U401.A (D1/D4), U402.33 (VS), U403.2 (D1/D4), U403.11 (D1/D4), U403.A (D1/D4), U501.2 (D1/D4), U501.11 (D1/D4), U501.A (D1/D4), U502.33 (VS), U503.2 (D1/D4), U503.11 (D1/D4), U503.A (D1/D4), U601.2 (D1/D4), U601.11 (D1/D4), U601.A (D1/D4), U602.33 (VS), U603.2 (D1/D4), U603.11 (D1/D4), U603.A (D1/D4); also elsewhere on the board

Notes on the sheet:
SD_MODE low to use ramp generator SPI_MODE high to enable SPI TST_MODE must be tied low
Temperature
Bootstrap capacitors: 220n for Q_G < 20nC. Our Q_G: 17nC. See TMC5160 p15, DMHT6016LFJ p2
BW=1/(2π*2k2*220n)=329Hz

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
